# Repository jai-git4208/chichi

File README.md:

# CHICHI - The Slap-Reactive Smart Lamp

CHICHI is a portable smart lamp shaped like a newly hatched chick in a cracked egg. It brings warm ambient light and playful personality wherever you go — responding to your touch with vibrant colors and breathing effects that make it feel alive.

## Why CHICHI?

In a world of cold screens and rigid devices, CHICHI brings warmth and emotion to your workspace or bedside. It's not just a lamp — it's a companion that responds to you, glows with you, and adds a touch of playfulness to your day. Whether you need focus lighting, a mood boost, or just something cute to brighten your desk, CHICHI is there.

## Features

- **Gesture-Controlled** - No buttons needed, just slap or tap
- **Adorable Design** - Shaped like a chick hatching from an egg
- **RGB LEDs** - WS2812B addressable LEDs for smooth animations
- **Portable & Rechargeable** - Built-in Li-Po battery with USB-C charging
- **Smart Interactions**:
  - **Single Slap** - Change colors
  - **Double Slap** - Power ON/OFF
  - **Idle Mode** - Soft breathing glow when untouched
- **Expandable** - ESP32-C3 with Wi-Fi & Bluetooth LE for future features
- **Compact & Cute** - Translucent 3D-printed shell with diffused lighting

## Schematic

The circuit is built around the ESP32-C3 Supermini microcontroller with:
- 2x WS2812B addressable RGB LEDs in series (D5 → D6)
- Piezo disc sensor connected directly to ESP32 GPIO
- Battery Charger 1A module with USB input
- LiPo battery providing power to entire system
- Simple, compact design with minimal external components

## PCB Design

Custom PCB designed for compact integration inside the egg shell:
- 2 WS2812B LEDs (D5 and D6) for efficient lighting
- ESP32-C3 Supermini module headers
- Battery Charger 1A module integration
- Piezo sensor connection pads
- LiPo battery connector

## Case Design

The 3D-printed case features:
- Translucent white PLA/PETG for frosted glow effect
- Two-piece egg design (cracked shell aesthetic)
- Internal cavity for PCB and battery
- Smooth surface finish for even light diffusion
- Compact size: 60-90mm tall (customizable)
- added a cyylinder to be able to open case easily.

Here's your updated BOM with prices and links:

## Bill of Materials (BOM)
| Component | Quantity | Price (INR) | Price (USD) | Link | Notes |
|-----------|----------|-------------|-------------|------|-------|
| ESP32-C3 Super Mini Dev Board | 1 | ₹249 | ~$3.00 | https://hubtronics.in/esp32-c3-super-mini-unsoldered?gad_source=1&gad_campaignid=22872103083&gbraid=0AAAAAD07y2daEUBDnuhJB0-3Eric8vzjN&gclid=CjwKCAiAl-_JBhBjEiwAn3rN7YRKA1vZ0fO1eb1FXJZS9X17QkaaFzzzENmHHNqNpg5i2XCcV6xIixoClmYQAvD_BwE | USB-C ESP32-C3 (shipping included) |
| WS2812B 5050 RGB LED Module | 2 | ₹16 | ~$0.19 | https://robu.in/product/sme-ws2812b-2020-addressable-rgb-pixel-led-worldsemi/?gad_source=1&gad_campaignid=17427802703&gbraid=0AAAAADvLFWdVZtRFmuZUVUdB3Vk_Cy1_z&gclid=CjwKCAiAl-_JBhBjEiwAn3rN7VQExptweZt_n9pNyBL5iHyxQKYkiyiE-ruWIlestUp_9RDfLFDnmhoCBksQAvD_BwE | Individually addressable LEDs |
| Piezoelectric Disc Sensor | 1 | ₹49 | ~$0.59 | https://electronicspices.com/product/35-mm-diameter-piezoelectric-sensor-plate-pack-of-5pcs | Very cheap single piezo disc |
| TP4056 Type-C Charging Module | 1 | ₹40 | ~$0.48 | https://robocraze.com/products/tp4056-battery-charger-c-type-module-with-protection-1?_pos=1&_sid=7bd707613&_ss=r | 1A Li-ion charger with protection |
| Li-Po Battery 3.7V 800mAh | 1 | ₹150 | ~$1.81 | https://quartzcomponents.com/products/3-7v-800mah-li-po-rechargeable-battery?_pos=1&_sid=3c18f12c0&_ss=r | Same capacity, much cheaper |
| MT3608 DC-DC Boost Converter | 1 | ₹35 | ~$0.42 | https://robokits.co.in/power-supply/dc-dc-power-supply/dc-dc-boost-25v-2a-mt3608 | Step-up to stable 5V |
| Custom PCB | 1 | ₹840 | ~$10.12 | - |  |
| 3D Printed Shell | 1 set | ₹420 | ~$5.06 | - |  |

---

### **Total Estimated Cost:**
- **₹1,799** (INR)
- **$21.67** (USD)

**Note:** Currency conversion based on approximate rate of ₹84 = $1 USD
BOM csv: [here!](https://github.com/jai-git4208/chichi/blob/main/resources/bom.csv)

## Interaction Modes

### Single Slap - Color Change(need to add btw)
A gentle slap on the shell cycles through vibrant color modes:
- **Warm White** - Cozy ambient lighting
- **Cool White** - Focus and productivity
- **Red Glow** - Evening/night mode
- **Blue Wave** - Calm and serene
- **Green Pulse** - Nature vibes
- **Purple Dream** - Creative energy
- **Rainbow Fade** - Playful and dynamic
- **Breathing Mode** - Slow pulsing (any color)

### Double Slap - Power Toggle
Two quick slaps turn CHICHI on or off. The LEDs fade smoothly to preserve battery and provide satisfying feedback.

### Idle Mode - Breathing Glow
When left alone, CHICHI breathes with a soft, warm glow — making it feel alive even when you're not interacting with it. Perfect for ambient mood lighting.

## Technical Specifications

### Power System
- **Battery**: 3.7V Li-Po (500-1200 mAh)
- **Charging**: Battery Charger 1A module via USB (5V input)
- **Runtime**: 3-6 hours depending on brightness
- **Power Distribution**: Direct battery power to ESP32 and LEDs
- **Deep Sleep**: Ultra-low power consumption when idle

### Microcontroller
- **Model**: ESP32-C3 Supermini
- **Core**: RISC-V single-core (32-bit)
- **Features**: Wi-Fi 802.11b/g/n, Bluetooth LE 5.0
- **Programming**: Arduino IDE / CircuitPython support
- **GPIO**: Digital I/O for LEDs and piezo sensor
- **Power**: 3.3V operation with onboard regulation

### Lighting Engine
- **LEDs**: 2x WS2812B addressable RGB (D5, D6)
- **Arrangement**: Series connection for synchronized lighting
- **Control**: Single data line from ESP32 GPIO
- **Voltage**: 5V LEDs powered by battery
- **Effects**: Solid colors, transitions, breathing, animations
- **Brightness**: Software-controlled PWM

### Sensor System
- **Type**: Piezo disc vibration sensor (piezo2)
- **Size**: 27-35mm diameter
- **Connection**: Direct to ESP32 GPIO
- **Detection**: Tap, slap, and pressure events
- **Signal Processing**: Software debouncing and threshold detection

## Design Files

- **PCB**: KiCad project files in `PCB/` folder
- **Case**: STEP and STL files in `CAD/` folder  
- **Firmware**: Arduino code in `Firmware/` folder
- **Resources**: Schematics and images in `resources/` folder

## Preferences

- **Shell Color**: Translucent White (frosted)
- **LED Ring**: Warm white base with RGB accents
- **Charging Port**: USB-C (accessible from bottom)

## Credits

Designed and built for the Hack Club Blueprint program.

**Designer**: JAIMIN PANSAL  
**GitHub**: [jai-git4208](https://github.com/jai-git4208)  
**License**: MIT

---

## With ❤️ by Jaimin

*"CHICHI isn't just a lamp — it's a little friend that glows with you."*

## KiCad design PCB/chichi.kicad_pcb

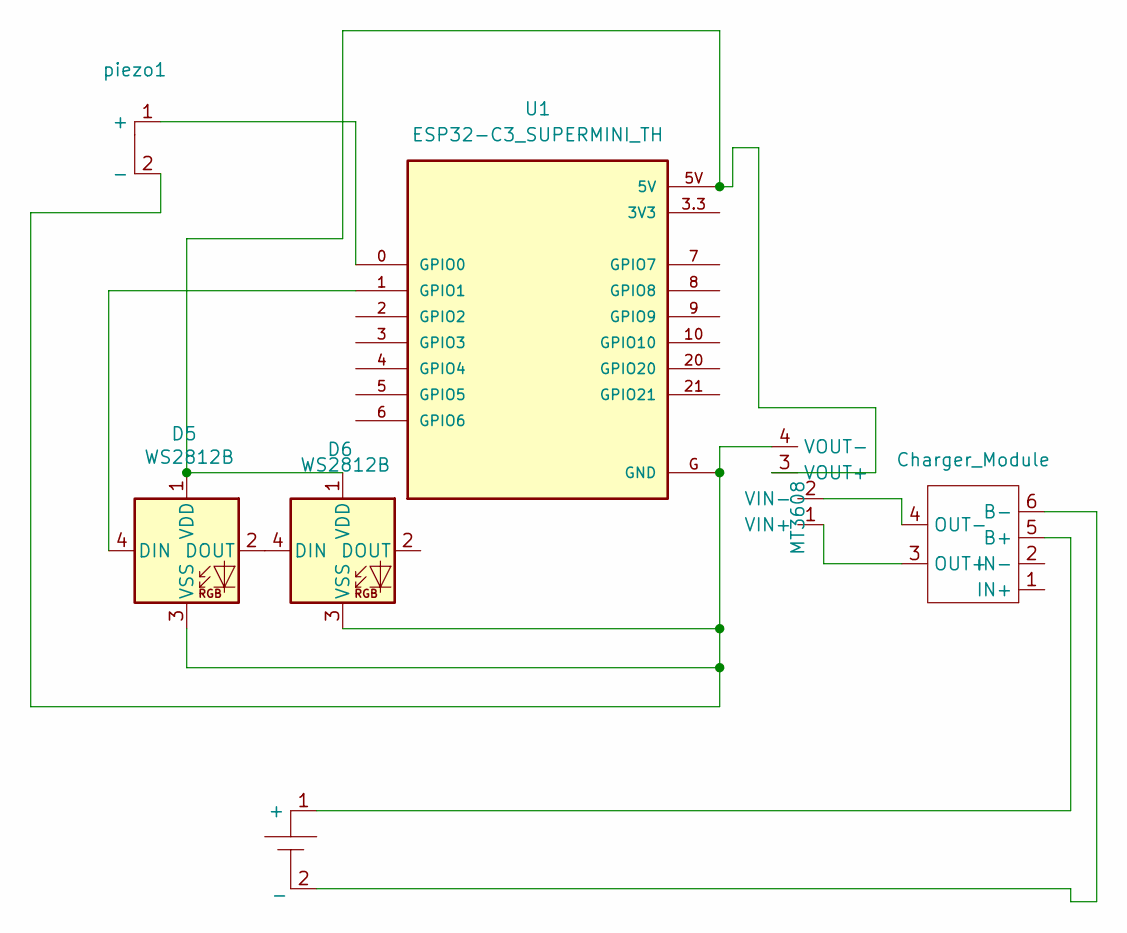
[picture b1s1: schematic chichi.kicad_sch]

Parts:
D5, D6: WS2812B; LED_WS2812B_PLCC4_5.0x5.0mm_P3.2mm
U1: ESP32-C3_SUPERMINI_TH; MODULE_ESP32-C3_SUPERMINI_TH
U2: Charger_Module; TP4056-18650
U3: LiPo
U4: MT3608; MT3608 Boost Converter
piezo1: piezo

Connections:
unnamed: D5.4 (DIN), U1.1 (GPIO1)
unnamed: D5.2 (DOUT), D6.4 (DIN)
unnamed: D5.1 (VDD), D6.1 (VDD), U1.5V, U4.3 (VOUT+)
unnamed: D5.3 (VSS), D6.3 (VSS), U1.G (GND), U4.4 (VOUT-), piezo1.2 (-)
unnamed: U1.0 (GPIO0), piezo1.1 (+)
unnamed: U2.5 (B+), U3.1 (+)
unnamed: U2.6 (B-), U3.2 (_)
unnamed: U2.3 (OUT+), U4.1 (VIN+)
unnamed: U2.4 (OUT-), U4.2 (VIN-)

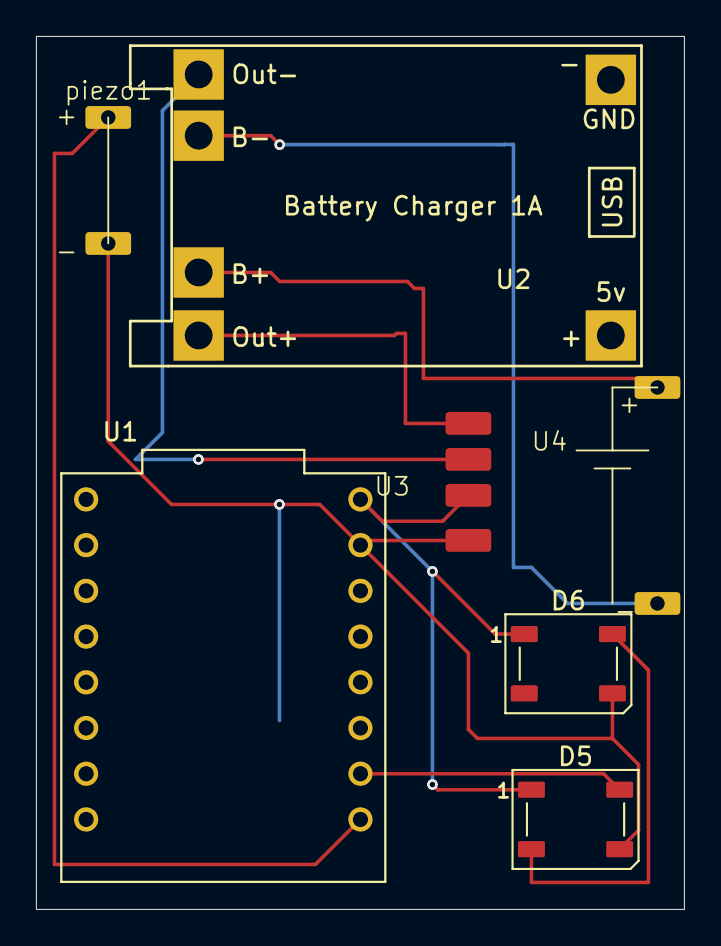
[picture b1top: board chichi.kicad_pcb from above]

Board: 2 copper layers, 36.0 x 48.5 mm, 7 parts (0 on the bottom side), 9 nets.

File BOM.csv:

Component,Quantity,Price (INR),Price (USD),Link,Notes
ESP32-C3 Super Mini Dev Board,1,249,~$3.00,https://hubtronics.in/esp32-c3-super-mini-unsoldered?gad_sou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,USB-C ESP32-C3 (shipping included)\
WS2812B 5050 RGB LED Module,2,16,~$0.19,https://robu.in/product/sme-ws2812b-2020-addressable-rgb-pix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,Individually addressable LEDs\
Piezoelectric Disc Sensor,1,49,~$0.59,https://electronicspices.com/product/35-mm-diameter-piezoele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,Very cheap single piezo disc\
TP4056 Type-C Charging Module,1,40,~$0.48,https://robocraze.com/products/tp4056-battery-charger-c-type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,1A Li-ion charger with protection\
Li-Po Battery 3.7V 800mAh,1,150,~$1.81,https://quartzcomponents.com/products/3-7v-800mah-li-po-rech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,Same capacity much cheaper\
MT3608 DC-DC Boost Converter,1,35,~$0.42,https://robokits.co.in/power-supply/dc-dc-power-supply/dc-dc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,Step-up to stable 5V\
Custom PCB,1,840,~$10.12,-,JlC PCB
3D Printed Shell,1,420,~$5.06,-,

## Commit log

2025-12-04 add License
2025-12-04 add readme.md
2025-12-05 feat: Add 3D PCB and case renders, update existing design images, and refine README documentation.
2025-12-06 Add MT3608 Module
2025-12-06 add BOM csv
